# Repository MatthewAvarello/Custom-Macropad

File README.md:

# Matthew's Lovely Macropad
My macropad is a 9 key macropad with a rotary encoder and an OLED screen! It uses KMK Firmware
## PCB
### Schematic:
The 9 keys are positioned in a 3x3 matrix, saving 3 gpio pins for other use

### PCB:

## CAD:
Two part Case is held by two m3 screws and heatset inserts

## Firmware:
* Uses KMK Firmware to power the PCB
* Keys act as a numberpad, unless 9 is held, in which the numbers turn into their respective function keys.
* Rotary encoder outputs arrows, button is unbound.
* OLED screen shows whether you are in Normal or function key mode
## BOM
* 9x Cherry MX Switches
* 9x DSA Keycaps
* 2x M3x5x4 HeatSet Inserts
* 2x M3x16mm Screws
* 9x Through the hole 1N4148 Diodes
* 1x 0.91" 128x32 OLED Screen
* 1x EC11E Rotary Encoder
* 1x XIAO RP2040
* 1x The Case (3d Printed Top and Bottom)
* 1x Soldering Iron (Unforunately do not have one)
## Room for Improvement
Looking back I would have changed the following if I had more time.

* Extended the top case print so that the case used 4 screws instead of 2. This would have probably helped structural stability
* Made the keybinds on the firmware more interesting and useful for every day use
* Made the wiring on the PCB more orderly instead of a jumbled mess 💀

## Random Other Notes
CAD was definetely the hardest part for me, arguably took around 80% of the total time I spent on the project. However, it was a great learning experience!

## Gallery

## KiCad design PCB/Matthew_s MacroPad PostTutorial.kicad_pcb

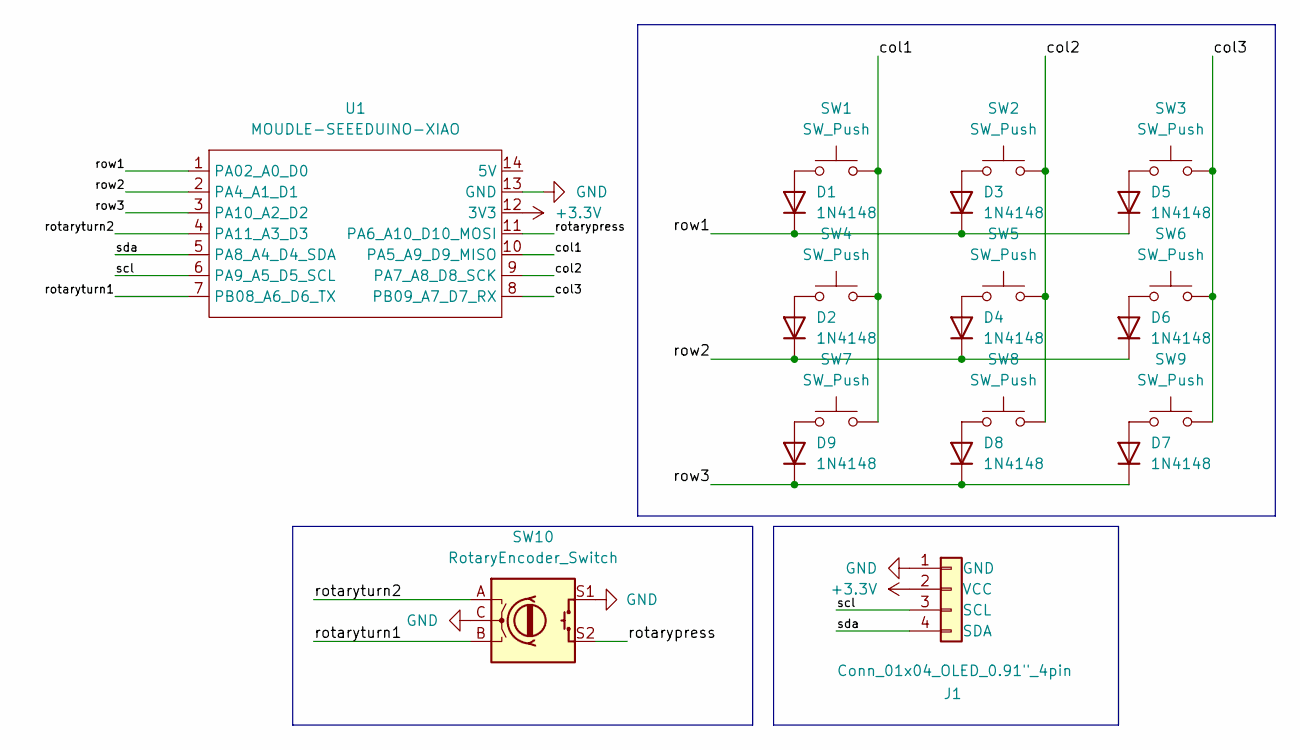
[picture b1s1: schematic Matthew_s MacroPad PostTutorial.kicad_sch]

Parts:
D1, D2, D3, D4, D5, D6, D7, D8, D9: 1N4148; D_DO-35_SOD27_P7.62mm_Horizontal
J1: Conn_01x04_OLED_0.91"_4pin; SSD1306-0.91-OLED-4pin-128x32
SW1, SW2, SW3, SW4, SW5, SW6, SW7, SW8, SW9: SW_Push; SW_Cherry_MX_1.00u_PCB
SW10: RotaryEncoder_Switch; RotaryEncoder_Alps_EC11E-Switch_Vertical_H20mm
U1: MOUDLE-SEEEDUINO-XIAO; XIAO-Generic-Hybrid-14P-2.54-21X17.8MM

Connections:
+3.3V: J1.2 (VCC), U1.12 (3V3)
/col1: SW1.2, SW4.2, SW7.2, U1.10 (PA5_A9_D9_MISO)
/col2: SW2.2, SW5.2, SW8.2, U1.9 (PA7_A8_D8_SCK)
/col3: SW3.2, SW6.2, SW9.2, U1.8 (PB09_A7_D7_RX)
/rotarypress: SW10.S2, U1.11 (PA6_A10_D10_MOSI)
/rotaryturn1: SW10.B, U1.7 (PB08_A6_D6_TX)
/rotaryturn2: SW10.A, U1.4 (PA11_A3_D3)
/row1: D1.1 (K), D3.1 (K), D5.1 (K), U1.1 (PA02_A0_D0)
/row2: D2.1 (K), D4.1 (K), D6.1 (K), U1.2 (PA4_A1_D1)
/row3: D7.1 (K), D8.1 (K), D9.1 (K), U1.3 (PA10_A2_D2)
/scl: J1.3 (SCL), U1.6 (PA9_A5_D5_SCL)
/sda: J1.4 (SDA), U1.5 (PA8_A4_D4_SDA)
GND: J1.1 (GND), SW10.C, SW10.S1, U1.13 (GND)
unnamed: D1.2 (A), SW1.1
unnamed: D2.2 (A), SW4.1
unnamed: D3.2 (A), SW2.1
unnamed: D4.2 (A), SW5.1
unnamed: D5.2 (A), SW3.1
unnamed: D6.2 (A), SW6.1
unnamed: D7.2 (A), SW9.1
unnamed: D8.2 (A), SW8.1
unnamed: D9.2 (A), SW7.1

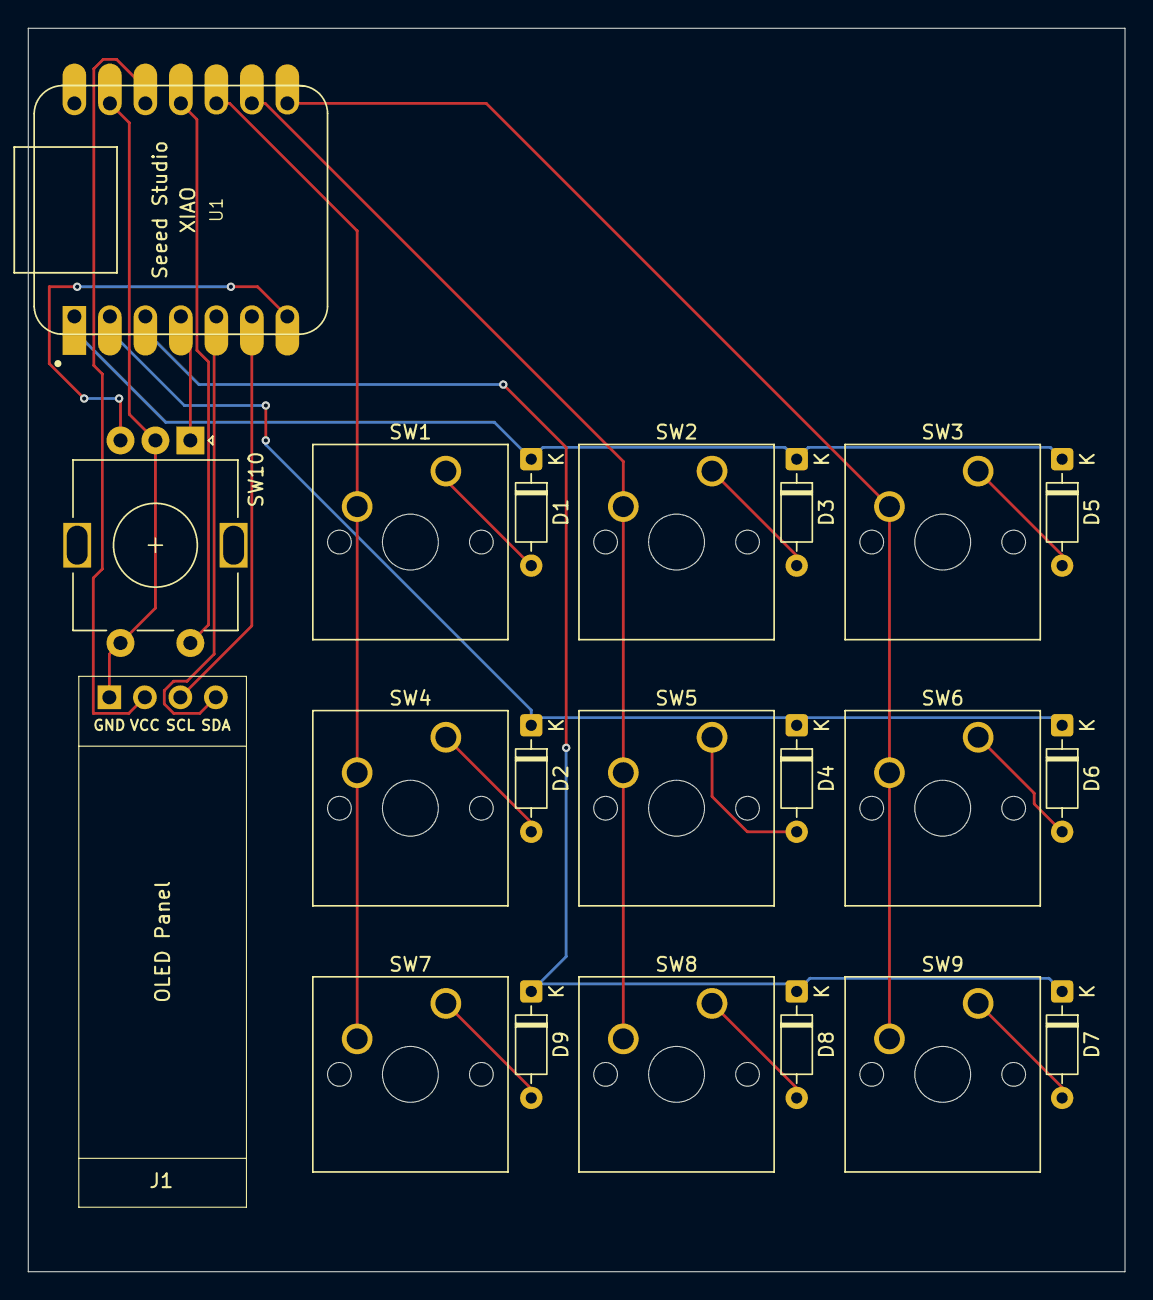
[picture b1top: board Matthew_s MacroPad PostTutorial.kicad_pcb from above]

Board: 2 copper layers, 78.5 x 89.0 mm, 21 parts (0 on the bottom side), 22 nets.

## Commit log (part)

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2026-04-01 Project Ready for Submission
2026-04-01 Fix typo in CAD time description
    Corrected a typo in the README regarding CAD time spent.
2026-04-04 Fixed Switch alignment issue
